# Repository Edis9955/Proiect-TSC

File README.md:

# Diagrama Bloc

# Bill of Materials

| Componenta | Descriere | Cumpara | Datasheet |
|------------|-----------|----------------|--------------|
| ESP32-C6-WROOM-1-N8 | Microcontroler cu Wi-Fi 6, BLE 5.0 | [Mouser](https://ro.mouser.com/ProductDetail/Espressif-Systems/ESP32-C6-WROOM-1-N8) | [Datasheet](https://www.espressif.com/sites/default/files/documentation/esp32-c6-wroom-1_wroom-1u_datasheet_en.pdf) |
| BME680 | Senzor temperatură, umiditate, presiune, VOC | [Mouser](https://ro.mouser.com/ProductDetail/Bosch-Sensortec/BME680) | [Datasheet](https://www.bosch-sensortec.com/media/boschsensortec/downloads/datasheets/bst-bme680-ds001.pdf) |
| DS3231SN | Ceas în timp real | [Mouser](https://ro.mouser.com/ProductDetail/Analog-Devices/DS3231SN) | [Datasheet](https://www.analog.com/media/en/technical-documentation/data-sheets/DS3231.pdf) |
| W25Q512JVEIQ | Memorie Flash 64MB | [Mouser](https://ro.mouser.com/ProductDetail/Winbond/W25Q512JVEIQ) | [Datasheet](https://www.winbond.com/resource-files/W25Q512JV%20SPI%20RevB%2006252019%20KMS.pdf) |
| MicroSD Slot (112A-TAAR-R03) | Slot card microSD | [Mouser](https://ro.mouser.com/ProductDetail/Attend/112A-TAAR-R03) | [Datasheet](https://www.attend.com.tw/data/download/file/112A-TAAR-R03_Spec.pdf) |
| MCP73831T-5ACI/OT | Încărcător baterie | [Mouser](https://ro.mouser.com/ProductDetail/Microchip-Technology/MCP73831T-5ACI-OT) | [Datasheet](https://ww1.microchip.com/downloads/en/DeviceDoc/MCP73831-Family-Data-Sheet-DS20001984H.pdf) |
| MAX17048G+T10 | Indicator nivel baterie | [Mouser](https://ro.mouser.com/ProductDetail/Analog-Devices/MAX17048G%2BT10) | [Datasheet](https://www.analog.com/media/en/technical-documentation/data-sheets/MAX17048-MAX17049.pdf) |
| XC6220A331MR-G | Regulator 3.3V | [Mouser](https://ro.mouser.com/ProductDetail/Torex-Semiconductor/XC6220A331MR-G) | [Datasheet](https://www.torexsemi.com/file/xc6220/XC6220.pdf) |
| USB4110-GF-A | Conector USB-C | [Mouser](https://ro.mouser.com/ProductDetail/GCT/USB4110-GF-A) | [Datasheet](https://gct.co/files/drawings/usb4110.pdf) |
| CPH3225A | Supercondensator pentru ceas | [Mouser](https://ro.mouser.com/ProductDetail/Seiko-Instruments/CPH3225A) | [Datasheet](https://mm.digikey.com/Volume0/opasdata/d220001/medias/docus/6537/rev05-CPHCPM.pdf) |
| DMG2305UX-7 | MOSFET P-Channel | [Mouser](https://ro.mouser.com/ProductDetail/Diodes-Incorporated/DMG2305UX-7) | [Datasheet](https://www.diodes.com/assets/Datasheets/DMG2305UX.pdf) |
| SI1308EDL-T1-GE3 | MOSFET N-Channel | [Mouser](https://ro.mouser.com/ProductDetail/Vishay-Siliconix/SI1308EDL-T1-GE3) | [Datasheet](https://www.vishay.com/docs/63399/si1308edl.pdf) |
| USBLC6-2SC6Y | Protecție ESD USB | [Mouser](https://ro.mouser.com/ProductDetail/STMicroelectronics/USBLC6-2SC6Y) | [Datasheet](https://www.st.com/resource/en/datasheet/usblc6-2.pdf) |
| PGB1010603MR | Protecție ESD | [Mouser](https://ro.mouser.com/ProductDetail/Littelfuse/PGB1010603MR) | [Datasheet](https://www.littelfuse.com/~/media/electronics/datasheets/esd_protection/littelfuse_pulseguard_esd_pgb1_series_datasheet.pdf) |
| BD5229G-TR | Detector tensiune | [Mouser](https://ro.mouser.com/ProductDetail/ROHM-Semiconductor/BD5229G-TR) | [Datasheet](https://fscdn.rohm.com/en/products/databook/datasheet/ic/power/voltage_detector/bd52xxg-e.pdf) |
| FH34SRJ-24S-0.5SH(99) | Conector FFC/FPC e-paper | [Mouser](https://ro.mouser.com/ProductDetail/Hirose-Connector/FH34SRJ-24S-0.5SH99) | [Datasheet](https://www.hirose.com/product/document?clcode=&productname=&series=FH34SRJ&documenttype=Catalog&lang=en) |
| 744043680 | Inductor | [Mouser](https://ro.mouser.com/ProductDetail/Wurth-Elektronik/744043680) | [Datasheet](https://www.we-online.com/components/products/datasheet/744043680.pdf) |
| EVQPUJ02K | Buton tactil | [Mouser](https://ro.mouser.com/ProductDetail/Panasonic/EVQPUJ02K) | [Datasheet](https://www.lcsc.com/datasheet/lcsc_datasheet_2201121800_PANASONIC-EVQPUJ02K_C2936858.pdf) |
| KP-1608SURCK | LED indicator | [Mouser](https://ro.mouser.com/ProductDetail/Kingbright/KP-1608SURCK) | [Datasheet](https://media.elv.com/file/107153_led_surck1608_data.pdf) |

# Functionalitati Hardware
### ESP32-C6-WROOM-1-N8
- MCU principal, Wi-Fi 6, Bluetooth 5
- Interfețe: SPI, I2C, UART, GPIO
- 160MHz, 512KB SRAM, 8MB Flash

### Senzor BME688
- Măsoară: temperatură, umiditate, presiune, VOC
- I2C, consum redus: <1mA

### Ecran E-Paper
- Diagonală: 7.5”
- Conectare prin SPI
- Consum 0 în stare statică

### Sistem de Alimentare
- Baterie: 3.7V Li-Po 2500mAh
- Încărcare: MCP73831, max 1A
- Monitorizare: MAX17048 (Fuel Gauge)
- Consum tipic:
- Activ: ~150mA
- Standby: ~10mA
- Deep Sleep: <50µA
- Autonomie: ~250h la 10mA

### Conectivitate USB-C
- Încărcare & date (USB 2.0)
- Protecție ESD: USBLC6-2SC6Y

# Descriere pini

| Pin  | Funcție        | Componentă          | Descriere Utilizare           |
|-----:|:---------------|:--------------------|:------------------------------|
| EN  | RESET    | Resetare sistem               |Pin pentru resetare
| GPIO0  | BOOT_BUTTON    | Buton               | Boot mode la pornire          |
| GPIO1  | RESET_BUTTON   | Buton               | Reset manual                  |
| GPIO2  | CHANGE_BUTTON  | Buton               | Navigare meniu                |
| GPIO3  | EPD_CS         | Display E-Paper     | Chip Select (SPI)             |
| GPIO4  | EPD_DC         | Display E-Paper     | Data/Command control          |
| GPIO5  | EPD_RST        | Display E-Paper     | Reset ecran                   |
| GPIO6  | EPD_BUSY       | Display E-Paper     | Semnal stare refresh          |
| GPIO7  | SPI_MOSI       | Display, Flash, SD  | Master Out Slave In (SPI)     |
| GPIO8  | SPI_MISO       | Display, Flash, SD  | Master In Slave Out (SPI)     |
| GPIO9  | SPI_SCK        | Display, Flash, SD  | Clock SPI                     |
| GPIO10 | FLASH_CS       | W25Q512JVEIQ        | Chip Select pentru Flash      |
| GPIO11 | SD_CS          | Micro SD (opțional) | Chip Select card SD           |
| GPIO12 | I2C_SDA        | BME680, MAX17048, DS3231 | Linie date I2C          |
| GPIO13 | I2C_SCL        | BME680, MAX17048, DS3231 | Linie clock I2C         |    
| GPIO14 | CHG_LED        | LED încărcare       | Status încărcare              |
| GPIO15 | UART_TX        | Debugging           | TX serial                     |
| GPIO16 | UART_RX        | Debugging           | RX serial                     |
| GPIO17 | USB_D+         | USB-C               | Linie date USB +              |
| GPIO18 | USB_D-         | USB-C               | Linie date USB – 
| GPIO21   | SDA          | Linie date I²C                   | Comun pentru senzori si RTC            |
| GPIO22   | SCL          | Linie ceas I²C                   | Semnal comun de ceas I²C               |
| GPIO23   | EPD_RST      | Resetare e-paper                 | Resetare hardware pentru afișaj        |
| TXD0   | TX           | Transmitere UART (depanare)      | Punct test pentru depanare             |
| RXD0   | RX           | Recepție UART (depanare)         | Punct test pentru depanare             |   |

## observatii:
- fisierul Mechanical si Images nu au fost inca populate
- componentele SPI ESD Protection Lines sunt foarte grupate
- toate test pad-urile sunt pe pcb, desi in model doar 5 erau

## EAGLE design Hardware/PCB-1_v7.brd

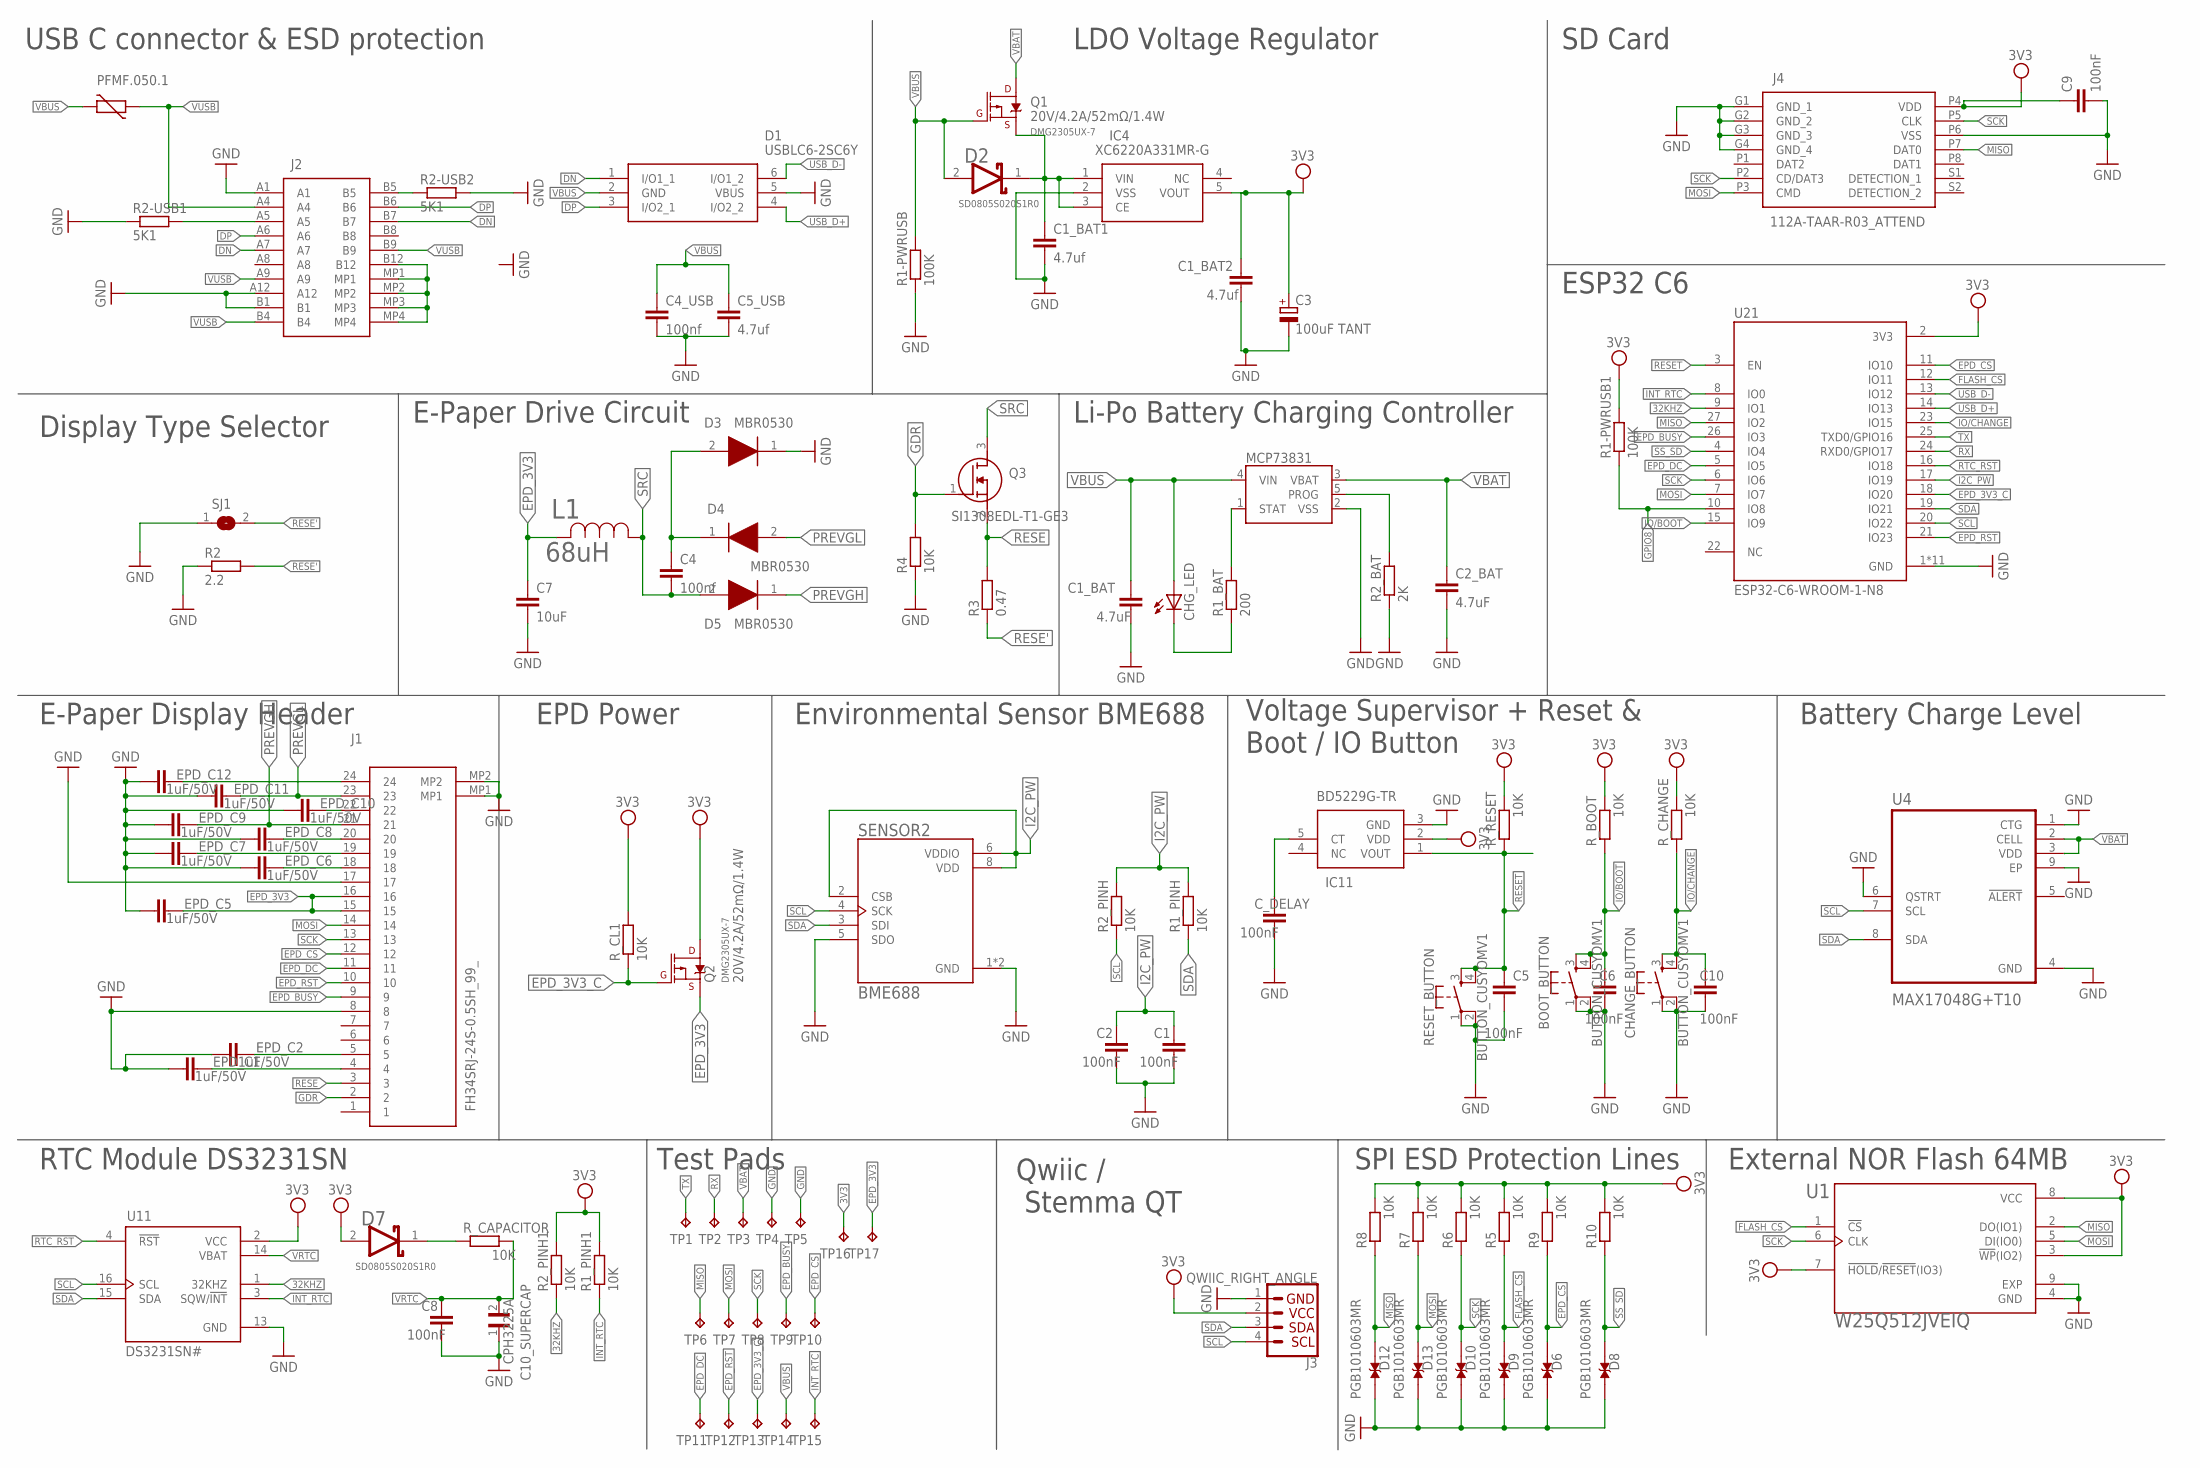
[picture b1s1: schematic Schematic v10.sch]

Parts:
BOOT_BUTTON: BUTTON_CUSYOMV1; MYBUTTON
C1, C2, C5, C6, C8, C9, C10: 100nF; EAGLE-LTSPICE_C0402
C1_BAT, C2_BAT: 4.7uF; EAGLE-LTSPICE_C0402
C1_BAT1, C1_BAT2, C5_USB: 4.7uf; EAGLE-LTSPICE_C0402
C3: 100uF TANT; RCL_CT3528
C4, C4_USB: 100nf; EAGLE-LTSPICE_C0402
C7: 10uF; EAGLE-LTSPICE_C0402
C10_SUPERCAP: CPH3225A; CAPCP3225X100N
CHANGE_BUTTON: BUTTON_CUSYOMV1; MYBUTTON
CHG_LED: ADAFRUIT_LEDCHIP-LED0603; ADAFRUIT_CHIP-LED0603
C_DELAY: 100nF; EAGLE-LTSPICE_C0402
D1: USBLC6-2SC6Y; SOT95P280X145-6N
D2, D7: ESP32_WROVER_AVX---SD0805S020S1R0_AVX_SD0805S020S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; ESP32_WROVER_AVX---SD0805S020S1R0_AVX_SD0805S020S1R0_0
D3, D4, D5: MBR0530; SOD3716X135N
D6, D8, D9, D10, D12, D13: PGB1010603MR; DIOC1608X36N
EPD_C1, EPD_C2, EPD_C5, EPD_C6, EPD_C7, EPD_C8, EPD_C9, EPD_C10, EPD_C11, EPD_C12: 1uF/50V; EAGLE-LTSPICE_C0402
IC4: XC6220A331MR-G; SOT95P280X120-5N
IC11: BD5229G-TR; SOT95P280X125-5N
J1: FH34SRJ-24S-0.5SH_99_; FH34SRJ24S05SH99
J2: SAMACSYS_PARTS_USB4110-GF-A; SAMACSYS_PARTS_USB4110GFA
J3: QWIIC_RIGHT_ANGLE; JST04_1MM_RA
J4: 112A-TAAR-R03_ATTEND; 112ATAARR03ATTEND
L1: 68uH; IND_4828-WE-TPC_WRE
MCP73831: ESP32_WROVER_SPARKFUN-IC-POWER_MCP73831; ESP32_WROVER_SPARKFUN-IC-POWER_SOT23-5
PFMF.050.1: ESP32C6_VARISTORCN1812; ESP32C6_VARISTOR_CT/CN1812
Q1, Q2: 20V/4.2A/52mΩ/1.4W; ESP32_WROVER_SPARKFUN-DISCRETESEMI_SOT23-3
Q3: SI1308EDL-T1-GE3; SOT65P210X110-3N
R1-PWRUSB, R1-PWRUSB1: 100K; ESP32_WROVER_EAGLE-LTSPICE_R0402
R1_BAT: 200; ESP32_WROVER_EAGLE-LTSPICE_R0402
R1_PINH, R1_PINH1, R2_PINH, R2_PINH1, R4, R5, R6, R7, R8, R9, R10: 10K; ESP32_WROVER_EAGLE-LTSPICE_R0402
R2: 2.2; ESP32_WROVER_EAGLE-LTSPICE_R0402
R2-USB1, R2-USB2: 5K1; ESP32_WROVER_EAGLE-LTSPICE_R0402
R2_BAT: 2K; ESP32_WROVER_EAGLE-LTSPICE_R0402
R3: 0.47; ESP32_WROVER_EAGLE-LTSPICE_R0402
RESET_BUTTON: BUTTON_CUSYOMV1; MYBUTTON
R_BOOT: 10K; ESP32_WROVER_EAGLE-LTSPICE_R0402
R_CAPACITOR: 10K; ESP32_WROVER_EAGLE-LTSPICE_R0402
R_CHANGE: 10K; ESP32_WROVER_EAGLE-LTSPICE_R0402
R_CL1: 10K; ESP32_WROVER_EAGLE-LTSPICE_R0402
R_RESET: 10K; ESP32_WROVER_EAGLE-LTSPICE_R0402
SENSOR2: BME688; ESP32_WROVER_BME680_PSON80P300X300X100-8N
SJ1: SJ
TP1, TP2, TP3, TP4, TP5, TP6, TP7, TP8, TP9, TP10, TP11, TP12, TP13, TP14, TP15, TP16, TP17: TPTP20R; TP20R
U1: W25Q512JVEIQ; SON127P600X800X80-9N
U4: MAX17048G+T10; SON50P200X200X80-9N
U11: DS3231SN#; SOIC127P1032X265-16N
U21: ESP32-C6-WROOM-1-N8; XCVR_ESP32-C6-WROOM-1-N8

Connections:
3V3: C1_BAT2.1, C3.+, C9.1, D7.2 (ANODE), IC4.5 (VOUT), IC11.2 (VDD), J3.2, J4.P4 (VDD), Q2.3 (D), R1-PWRUSB1.2, R1_PINH1.2, R2_PINH1.2, R5.2, R6.2, R7.2, R8.2, R9.2, R10.2, R_BOOT.2, R_CHANGE.2, R_CL1.2, R_RESET.2, TP16.TP, U1.3 (!WP!(IO2)), U1.7 (!HOLD!/!RESET!(IO3)), U1.8 (VCC), U11.2 (VCC), U21.2 (3V3)
32KHZ: R2_PINH1.1, U11.1 (32KHZ), U21.9 (IO1)
DN: D1.1 (I/O1_1), J2.A7, J2.B7
DP: D1.3 (I/O2_1), J2.A6, J2.B6
EPD_3V3: C7.1, EPD_C5.2, J1.15, J1.16, L1.2, Q2.2 (S), TP17.TP
EPD_3V3_C: Q2.1 (G), R_CL1.1, TP13.TP, U21.18 (IO20)
EPD_BUSY: J1.9, TP9.TP, U21.26 (IO3)
EPD_CS: D6.2, J1.12, R9.1, TP10.TP, U21.11 (IO10)
EPD_DC: J1.11, TP11.TP, U21.5 (IO5)
EPD_RST: J1.10, TP12.TP, U21.21 (IO23)
FLASH_CS: D9.2, R5.1, U1.1 (!CS), U21.12 (IO11)
GDR: J1.2, Q3.1 (G), R4.2
GPIO8: R1-PWRUSB1.1, U21.10 (IO8)
I2C_PW: C1.1, C2.1, R1_PINH.2, R2_PINH.2, SENSOR2.2 (CSB), SENSOR2.6 (VDDIO), SENSOR2.8 (VDD), U21.17 (IO19)
INT_RTC: R1_PINH1.1, TP15.TP, U11.3 (SQW/!INT), U21.8 (IO0)
IO/BOOT: BOOT_BUTTON.3, BOOT_BUTTON.4, C6.1, R_BOOT.1, U21.15 (IO9)
IO/CHANGE: C10.1, CHANGE_BUTTON.3, CHANGE_BUTTON.4, R_CHANGE.1, U21.23 (IO15)
MISO: D12.2, J4.P7 (DAT0), R8.1, TP6.TP, U1.2 (DO(IO1)), U21.27 (IO2)
MOSI: D13.2, J1.14, J4.P3 (CMD), R7.1, TP7.TP, U1.5 (DI(IO0)), U21.7 (IO7)
unnamed: J2.A5, R2-USB1.2
unnamed: C1_BAT1.1, D2.1 (CATHODE), IC4.1 (VIN), IC4.3 (CE), Q1.2 (S)
unnamed: EPD_C12.2, J1.24
unnamed: CHG_LED.C, R1_BAT.1
unnamed: C4.1, D3.2 (A), D4.1 (K)
unnamed: MCP73831.1 (STAT), R1_BAT.2
unnamed: MCP73831.5 (PROG), R2_BAT.2
unnamed: EPD_C10.2, J1.22
unnamed: C_DELAY.1, IC11.5 (CT)
unnamed: EPD_C8.2, J1.20
unnamed: EPD_C6.2, J1.18
unnamed: EPD_C7.2, J1.19
unnamed: D7.1 (CATHODE), R_CAPACITOR.1
unnamed: EPD_C2.2, J1.5
unnamed: EPD_C1.2, J1.4
PREVGH: D5.1 (K), EPD_C9.2, J1.21
PREVGL: D4.2 (A), EPD_C11.2, J1.23
RESE: J1.3, Q3.2 (S), R3.2
RESE': R2.2, R3.1, SJ1.2
RESET: C5.1, IC11.1 (VOUT), RESET_BUTTON.3, RESET_BUTTON.4, R_RESET.1, U21.3 (EN)
RTC_RST: U11.4 (!RST), U21.16 (IO18)
RX: TP2.TP, U21.24 (RXD0/GPIO17)
SCK: D10.2, J1.13, J4.P2 (CD/DAT3), J4.P5 (CLK), R6.1, TP8.TP, U1.6 (CLK), U21.6 (IO6)
SCL: J3.4, R2_PINH.1, SENSOR2.4 (SCK), U4.7 (SCL), U11.16 (SCL), U21.20 (IO22)
SDA: J3.3, R1_PINH.1, SENSOR2.3 (SDI), U4.8 (SDA), U11.15 (SDA), U21.19 (IO21)
SRC: C4.2, D5.2 (A), L1.1, Q3.3 (D)
SS_SD: D8.2, R10.1, U21.4 (IO4)
TX: TP1.TP, U21.25 (TXD0/GPIO16)
USB_D+: D1.4 (I/O2_2), U21.14 (IO13)
USB_D-: D1.6 (I/O1_2), U21.13 (IO12)
VBAT: C2_BAT.1, MCP73831.3 (VBAT), Q1.3 (D), TP3.TP, U4.2 (CELL), U4.3 (VDD)
VBUS: C1_BAT.1, C4_USB.1, C5_USB.1, CHG_LED.A, D1.2 (GND), D2.2 (ANODE), MCP73831.4 (VIN), PFMF.050.1.2, Q1.1 (G), R1-PWRUSB.2, TP14.TP
VRTC: C8.1, C10_SUPERCAP.2, R_CAPACITOR.2, U11.14 (VBAT)
VUSB: J2.A4, J2.A9, J2.B4, J2.B9, PFMF.050.1.1

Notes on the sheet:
USB C connector & ESD protection
LDO Voltage Regulator
SD Card
ESP32 C6
Battery Charge Level
External NOR Flash 64MB
SPI ESD Protection Lines
Voltage Supervisor + Reset & Boot / IO Button
Li-Po Battery Charging Controller
Environmental Sensor BME688
EPD Power
E-Paper Display Header
Display Type Selector
E-Paper Drive Circuit
RTC Module DS3231SN
Test Pads
Qwiic / Stemma QT

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
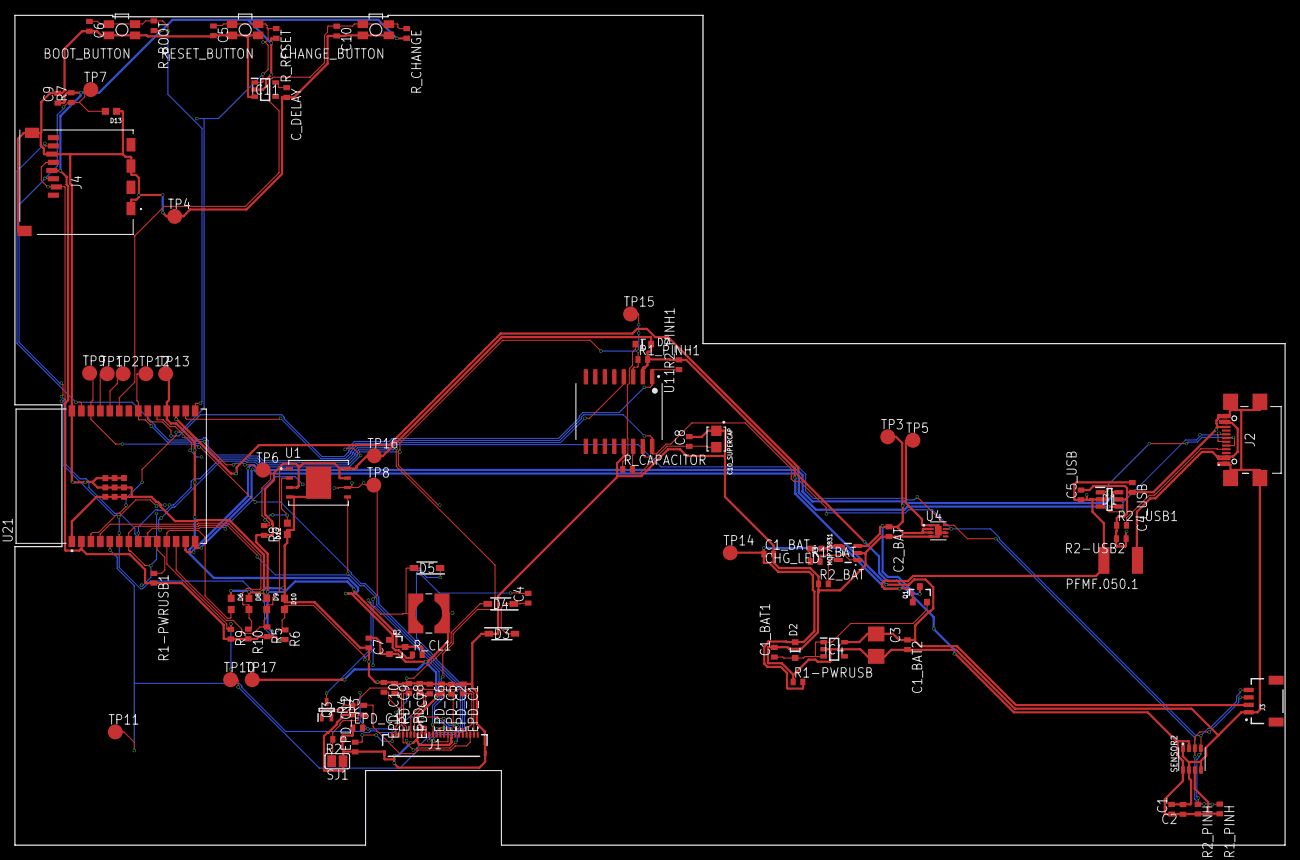
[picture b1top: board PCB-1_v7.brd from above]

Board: 2 copper layers, 170.1 x 111.2 mm, 103 parts (0 on the bottom side), 54 nets.

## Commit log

2025-04-06 ceva
2025-04-15 updated pcb to fix routing + component placement

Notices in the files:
parts and their libraries:
COPYRIGHT: Copyright (C) 2024 Ultra Librarian. All rights reserved.
